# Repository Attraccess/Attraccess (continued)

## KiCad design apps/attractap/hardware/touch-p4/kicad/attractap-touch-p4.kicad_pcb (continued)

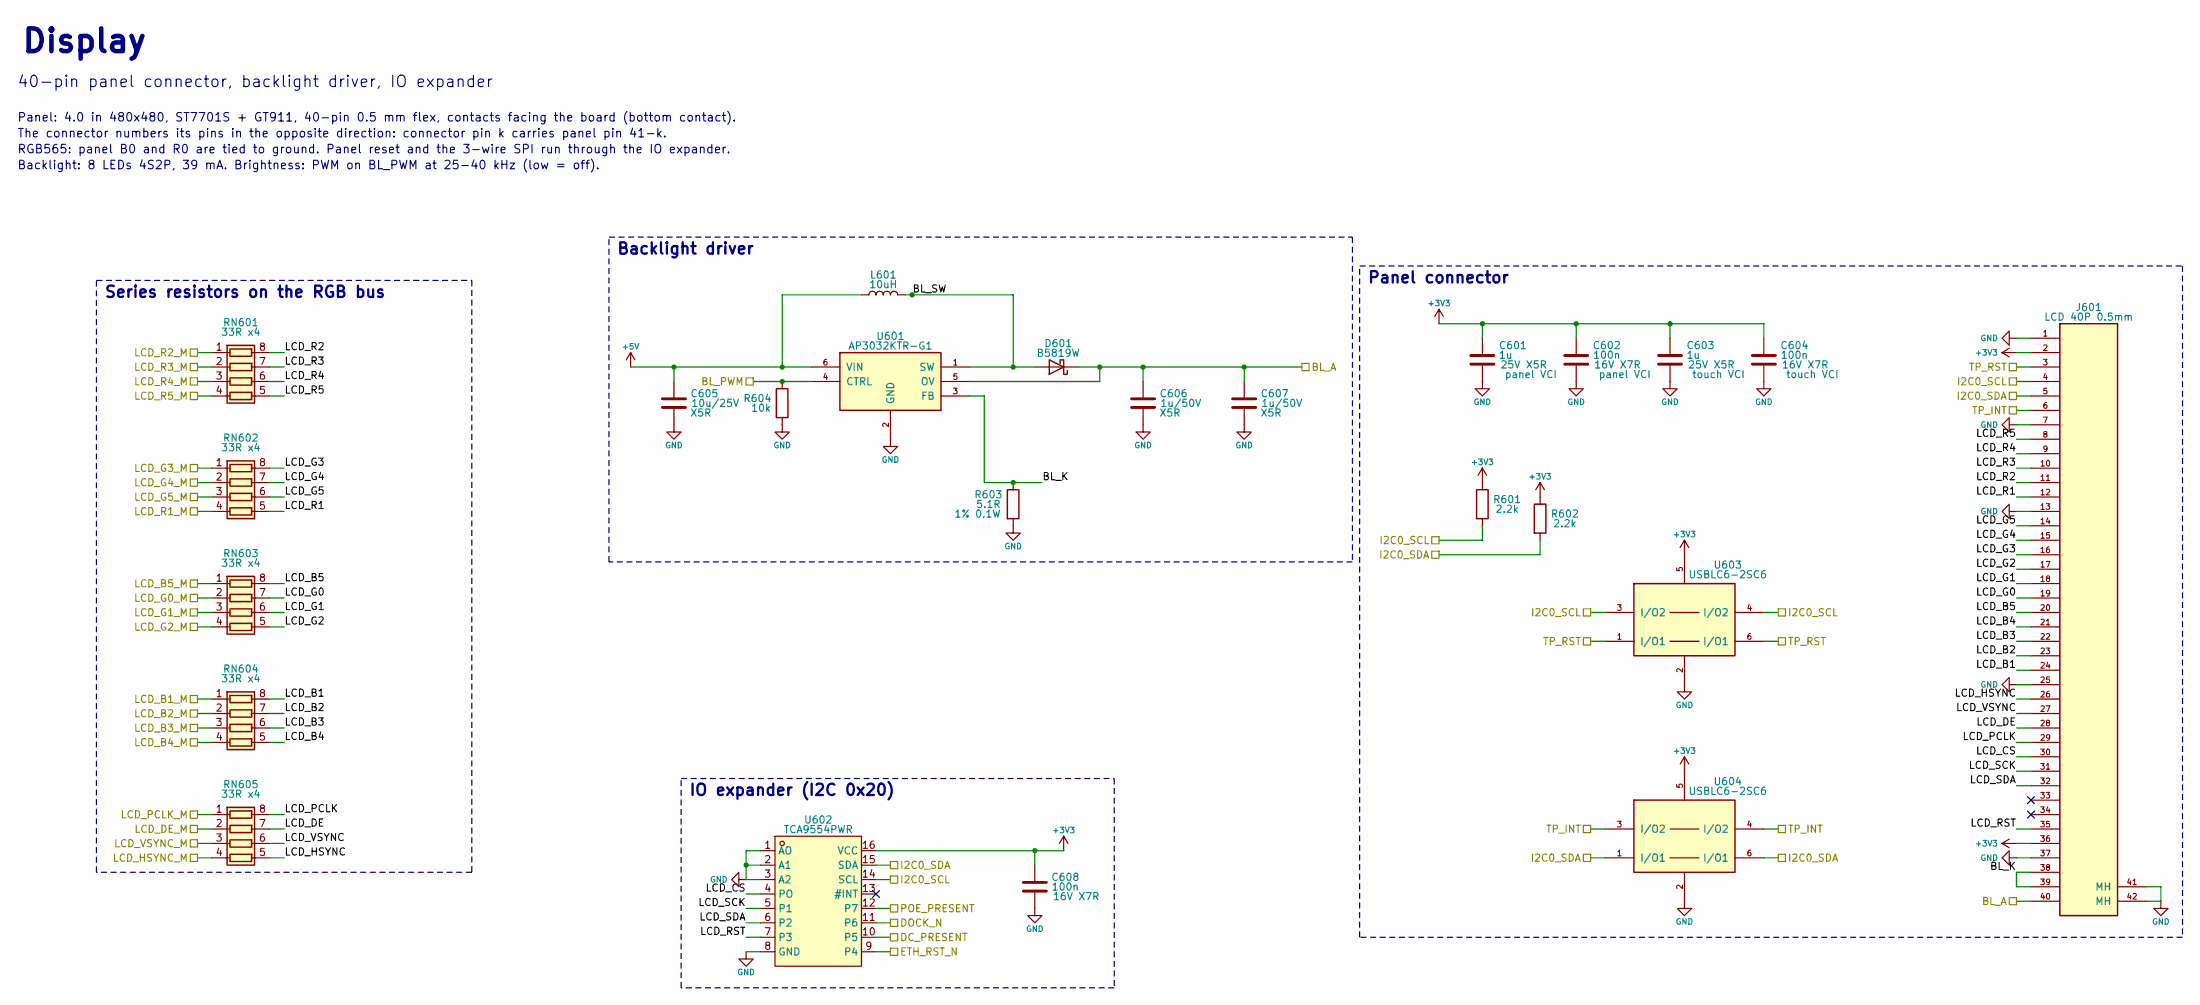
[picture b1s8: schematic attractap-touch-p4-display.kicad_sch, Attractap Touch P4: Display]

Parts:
C601, C603: 1u; C_0402_1005Metric; Rating 25V X5R; MPN CL05A105KA5NQNC; LCSC C52923
C602, C604, C608: 100n; C_0402_1005Metric; Rating 16V X7R; MPN CL05B104KO5NNNC; LCSC C1525
C605: 10u/25V; C_0805_2012Metric; Rating X5R; MPN CL21A106KAYNNNE; LCSC C15850
C606, C607: 1u/50V; C_0603_1608Metric; Rating X5R; MPN CL10A105KB8NNNC; LCSC C15849
D601: B5819W; SOD-123_L2.7-W1.6-LS3.7-RD-1; MPN B5819W; LCSC C8598
J601: LCD 40P 0.5mm; FPC-SMD_FH12-40S-0.5SH-55; MPN FH12-40S-0.5SH(55); LCSC C202114
L601: 10uH; IND-SMD_L3.0-W3.0_SWPA3010S; MPN SWPA3015S100MT; LCSC C45403
R601, R602: 2.2k; R_0402_1005Metric; Rating 1% 62.5mW; MPN 0402WGF2201TCE; LCSC C25879
R603: 5.1R; R_0603_1608Metric; Rating 1% 0.1W; MPN 0603WAF510KT5E; LCSC C25197
R604: 10k; R_0402_1005Metric; Rating 1% 62.5mW; MPN 0402WGF1002TCE; LCSC C25744
RN601, RN602, RN603, RN604, RN605: 33R x4; R_Array_Convex_4x0402; MPN 4D02WGJ0330TCE; LCSC C25501
U601: AP3032KTR-G1; SOT-23-6_L2.9-W1.6-P0.95-LS2.8-BR; MPN AP3032KTR-G1; LCSC C264086
U602: TCA9554PWR; TSSOP-16_L5.0-W4.4-P0.65-LS6.4-TL; MPN TCA9554PWR; LCSC C477924
U603, U604: USBLC6-2SC6; SOT-23-6_L2.9-W1.6-P0.95-LS2.8-BL; MPN USBLC6-2SC6; LCSC C7519

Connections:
+3V3: C601.1, C602.1, C603.1, C604.1, C608.1, J601.2, J601.36, R601.1, R602.1, U602.16 (VCC), U603.5, U604.5; also elsewhere on the board
+5V: C605.1, L601.1, U601.6 (VIN); also elsewhere on the board
/BL_A: C606.1, C607.1, D601.1 (K), J601.40, U601.5 (OV); also elsewhere on the board
/BL_PWM: R604.1, U601.4 (CTRL); also elsewhere on the board
/DC_PRESENT: U602.10 (P5); also elsewhere on the board
/DOCK_N: U602.11 (P6); also elsewhere on the board
/Display/BL_K: J601.38, J601.39, R603.1, U601.3 (FB)
/Display/BL_SW: D601.2 (A), L601.2, U601.1 (SW)
/Display/LCD_B1: J601.24, RN604.8 (R1.2)
/Display/LCD_B2: J601.23, RN604.7 (R2.2)
/Display/LCD_B3: J601.22, RN604.6 (R3.2)
/Display/LCD_B4: J601.21, RN604.5 (R4.2)
/Display/LCD_B5: J601.20, RN603.8 (R1.2)
/Display/LCD_CS: J601.30, U602.4 (PO)
/Display/LCD_DE: J601.28, RN605.7 (R2.2)
/Display/LCD_G0: J601.19, RN603.7 (R2.2)
/Display/LCD_G1: J601.18, RN603.6 (R3.2)
/Display/LCD_G2: J601.17, RN603.5 (R4.2)
/Display/LCD_G3: J601.16, RN602.8 (R1.2)
/Display/LCD_G4: J601.15, RN602.7 (R2.2)
/Display/LCD_G5: J601.14, RN602.6 (R3.2)
/Display/LCD_HSYNC: J601.26, RN605.5 (R4.2)
/Display/LCD_PCLK: J601.29, RN605.8 (R1.2)
/Display/LCD_R1: J601.12, RN602.5 (R4.2)
/Display/LCD_R2: J601.11, RN601.8 (R1.2)
/Display/LCD_R3: J601.10, RN601.7 (R2.2)
/Display/LCD_R4: J601.9, RN601.6 (R3.2)
/Display/LCD_R5: J601.8, RN601.5 (R4.2)
/Display/LCD_RST: J601.35, U602.7 (P3)
/Display/LCD_SCK: J601.31, U602.5 (P1)
/Display/LCD_SDA: J601.32, U602.6 (P2)
/Display/LCD_VSYNC: J601.27, RN605.6 (R3.2)
/ETH_RST_N: U602.9 (P4); also elsewhere on the board
/I2C0_SCL: J601.4, R601.2, U602.14 (SCL), U603.3 (I/O2), U603.4 (I/O2); also elsewhere on the board
/I2C0_SDA: J601.5, R602.2, U602.15 (SDA), U604.1 (I/O1), U604.6 (I/O1); also elsewhere on the board
/LCD_B1_M: RN604.1 (R1.1); also elsewhere on the board
/LCD_B2_M: RN604.2 (R2.1); also elsewhere on the board
/LCD_B3_M: RN604.3 (R3.1); also elsewhere on the board
/LCD_B4_M: RN604.4 (R4.1); also elsewhere on the board
/LCD_B5_M: RN603.1 (R1.1); also elsewhere on the board
/LCD_DE_M: RN605.2 (R2.1); also elsewhere on the board
/LCD_G0_M: RN603.2 (R2.1); also elsewhere on the board
/LCD_G1_M: RN603.3 (R3.1); also elsewhere on the board
/LCD_G2_M: RN603.4 (R4.1); also elsewhere on the board
/LCD_G3_M: RN602.1 (R1.1); also elsewhere on the board
/LCD_G4_M: RN602.2 (R2.1); also elsewhere on the board
/LCD_G5_M: RN602.3 (R3.1); also elsewhere on the board
/LCD_HSYNC_M: RN605.4 (R4.1); also elsewhere on the board
/LCD_PCLK_M: RN605.1 (R1.1); also elsewhere on the board
/LCD_R1_M: RN602.4 (R4.1); also elsewhere on the board
/LCD_R2_M: RN601.1 (R1.1); also elsewhere on the board
/LCD_R3_M: RN601.2 (R2.1); also elsewhere on the board
/LCD_R4_M: RN601.3 (R3.1); also elsewhere on the board
/LCD_R5_M: RN601.4 (R4.1); also elsewhere on the board
/LCD_VSYNC_M: RN605.3 (R3.1); also elsewhere on the board
/POE_PRESENT: U602.12 (P7); also elsewhere on the board
/TP_INT: J601.6, U604.3 (I/O2), U604.4 (I/O2); also elsewhere on the board
/TP_RST: J601.3, U603.1 (I/O1), U603.6 (I/O1); also elsewhere on the board
GND: C601.2, C602.2, C603.2, C604.2, C605.2, C606.2, C607.2, C608.2, J601.1, J601.7, J601.13, J601.25, J601.37, J601.41 (MH), J601.42 (MH), R603.2, R604.2, U601.2 (GND), U602.1 (AO), U602.2 (A1), U602.3 (A2), U602.8 (GND), U603.2, U604.2; also elsewhere on the board

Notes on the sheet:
Display
40-pin panel connector, backlight driver, IO expander
Panel: 4.0 in 480x480, ST7701S + GT911, 40-pin 0.5 mm flex, contacts facing the board (bottom contact).
The connector numbers its pins in the opposite direction: connector pin k carries panel pin 41-k.
RGB565: panel B0 and R0 are tied to ground. Panel reset and the 3-wire SPI run through the IO expander.
Backlight: 8 LEDs 4S2P, 39 mA. Brightness: PWM on BL_PWM at 25-40 kHz (low = off).
Panel connector
Series resistors on the RGB bus
Backlight driver
IO expander (I2C 0x20)

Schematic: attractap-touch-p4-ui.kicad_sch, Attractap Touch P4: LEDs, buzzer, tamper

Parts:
BZ701: MLT-8530; BUZ-SMD_4P-L8.5-W8.5-P8.50-BR; MPN MLT-8530; LCSC C94599
C701, C703, C704, C705, C706, C707, C708, C709, C710, C711, C713, C714, C716, C717, C718, C719, C720, C721, C722, C723, C724: 100n; C_0402_1005Metric; Rating 16V X7R; MPN CL05B104KO5NNNC; LCSC C1525
C702: 22u; C_0805_2012Metric; Rating 25V X5R; MPN CL21A226MAQNNNE; LCSC C45783
C712: 10u; C_0603_1608Metric; Rating 10V X5R; MPN CL10A106KP8NNNC; LCSC C19702
C715: 4.7u; C_0603_1608Metric; Rating 16V X5R; MPN CL10A475KO8NNNC; LCSC C19666
C725, C726: 100u/16V; CP_Elec_6.3x5.4; MPN FVH016ADA101M0654; LCSC C7469977
C727: 39p; C_0402_1005Metric; Rating 50V C0G; MPN CC0402JRNPO9BN390; LCSC C106223
D701, D702, D703, D704, D705, D706, D707, D708, D710, D711, D712, D713, D714, D715, D716, D717: SK6812MINI-E; LED_SK6812MINI-E_ReverseMount_Clear; MPN SK6812MINI-E; LCSC C5149201
D709: 1N4148W; SOD-123F_L2.7-W1.6-LS3.8-RD; MPN 1N4148W; LCSC C81598
Q701: AO3400A; SOT-23; MPN AO3400A; LCSC C20917
R701, R703: 100R; R_0402_1005Metric; Rating 1% 62.5mW; MPN 0402WGF1000TCE; LCSC C25076
R702: 10R; R_0603_1608Metric; Rating 5% 0.25W; MPN ESR03EZPJ100; LCSC C253327
R704, R705: 100k; R_0402_1005Metric; Rating 1% 62.5mW; MPN 0402WGF1003TCE; LCSC C25741
R706, R707: 10k; R_0402_1005Metric; Rating 1% 62.5mW; MPN 0402WGF1002TCE; LCSC C25744
R708: 91k; R_0402_1005Metric; Rating 1% 62.5mW; MPN 0402WGF9102TCE; LCSC C4147
R709: 2.2k; R_0402_1005Metric; Rating 1% 62.5mW; MPN 0402WGF2201TCE; LCSC C25879
TP814: ACC_INT; TestPoint_Pad_D1.5mm
TP815: PROX_INT; TestPoint_Pad_D1.5mm
U701: 74LV1T125; SOT-23-5_L3.0-W1.7-P0.95-LS2.8-BR; MPN SN74LV1T125DBVR; LCSC C473338
U702: LIS2DH12TR; LGA-12_2x2mm_P0.5mm; MPN LIS2DH12TR; LCSC C110926
U703: DRV5032FA; SOT-23; MPN DRV5032FADBZR; LCSC C140921
U704: VCNL4040M3OE; SENSORS-SMD_VCNL4040M3OE; MPN VCNL4040M3OE; LCSC C142526
U705: TPS2553DBVR; SOT-23-6_L2.9-W1.6-P0.95-LS2.8-BL; MPN TPS2553DBVR; LCSC C55266

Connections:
+3V3: C711.1, C712.1, C713.1, C714.1, C715.1, R706.1, R707.1, U702.2 (~CS), U702.9 (Vdd), U702.10 (Vdd_IO), U703.1 (VDD), U704.3 (VDD), U704.4 (ANODE); also elsewhere on the board
+5V: C702.1, C724.1, R702.1, U705.1 (IN), U705.3 (EN); also elsewhere on the board
/BUZZER: R703.1; also elsewhere on the board
/DOCK_N: U703.2 (OUT); also elsewhere on the board
/I2C0_SCL: U702.1 (SCL/SPC), U704.8 (SCLK); also elsewhere on the board
/I2C0_SDA: U702.4 (SDA/SDI), U704.7 (SDAT); also elsewhere on the board
/LED_DATA: R705.1, U701.2 (A); also elsewhere on the board
/UI/+5V_LED: C701.1, C703.1, C704.1, C705.1, C706.1, C707.1, C708.1, C709.1, C710.1, C716.1, C717.1, C718.1, C719.1, C720.1, C721.1, C722.1, C723.1, C725.1, C726.1, D701.3 (VDD), D702.3 (VDD), D703.3 (VDD), D704.3 (VDD), D705.3 (VDD), D706.3 (VDD), D707.3 (VDD), D708.3 (VDD), D710.3 (VDD), D711.3 (VDD), D712.3 (VDD), D713.3 (VDD), D714.3 (VDD), D715.3 (VDD), D716.3 (VDD), D717.3 (VDD), U701.5 (VCC), U705.6 (OUT)
/UI/ACC_INT: TP814.1, U702.12 (INT1)
/UI/ACC_SA0: R706.2, U702.3 (SA0/SDO)
/UI/BUZ_G: Q701.1 (G), R703.2, R704.1
/UI/BUZ_N: BZ701.2 (-), D709.2 (A), Q701.3 (D)
/UI/BUZ_P: BZ701.1 (+), D709.1 (K), R702.2
/UI/LED_D0: D701.2 (DIN), R701.2
/UI/LED_D1: D701.4 (DOUT), D702.2 (DIN)
/UI/LED_D2: D702.4 (DOUT), D703.2 (DIN)
/UI/LED_D3: D703.4 (DOUT), D704.2 (DIN)
/UI/LED_D4: D704.4 (DOUT), D705.2 (DIN)
/UI/LED_D5: D705.4 (DOUT), D706.2 (DIN)
/UI/LED_D6: D706.4 (DOUT), R709.1
/UI/LED_D6_F: C727.1, D707.2 (DIN), R709.2
/UI/LED_D7: D707.4 (DOUT), D708.2 (DIN)
/UI/LED_D8: D708.4 (DOUT), D710.2 (DIN)
/UI/LED_D9: D710.4 (DOUT), D711.2 (DIN)
/UI/LED_D10: D711.4 (DOUT), D712.2 (DIN)
/UI/LED_D11: D712.4 (DOUT), D713.2 (DIN)
/UI/LED_D12: D713.4 (DOUT), D714.2 (DIN)
/UI/LED_D13: D714.4 (DOUT), D715.2 (DIN)
/UI/LED_D14: D715.4 (DOUT), D716.2 (DIN)
/UI/LED_D15: D716.4 (DOUT), D717.2 (DIN)
/UI/LED_DATA_5V: R701.1, U701.4 (Y)
/UI/LED_ILIM: R708.1, U705.5 (ILIM)
/UI/PROX_INT: R707.2, TP815.1, U704.6 (INT)
/UI/PROX_K: U704.2 (CATHODE(SENSOR)), U704.5 (CATHODE(LED))
GND: C701.2, C702.2, C703.2, C704.2, C705.2, C706.2, C707.2, C708.2, C709.2, C710.2, C711.2, C712.2, C713.2, C714.2, C715.2, C716.2, C717.2, C718.2, C719.2, C720.2, C721.2, C722.2, C723.2, C724.2, C725.2, C726.2, C727.2, D701.1 (GND), D702.1 (GND), D703.1 (GND), D704.1 (GND), D705.1 (GND), D706.1 (GND), D707.1 (GND), D708.1 (GND), D710.1 (GND), D711.1 (GND), D712.1 (GND), D713.1 (GND), D714.1 (GND), D715.1 (GND), D716.1 (GND), D717.1 (GND), Q701.2 (S), R704.2, R705.2, R708.2, U701.1 (~OE), U701.3 (GND), U702.5 (RES), U702.6 (GND), U702.7 (GND), U702.8 (GND), U703.3 (GND), U704.1 (GND), U705.2 (GND); also elsewhere on the board

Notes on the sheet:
LEDs, buzzer, tamper
Addressable RGB LEDs, level shifter, buzzer driver, tamper sensors
16 reverse-mount LEDs in a ring, shining through the board. Data: D701 -> D708, D710 -> D717.
Buzzer: drive BUZZER with a 2.7 kHz square wave (LEDC). Its coil is between pads 1 and 2;
pads 3 and 4 only hold the part. R705 keeps the LED data line low while the MCU is in reset.
LED supply: U705 limits the ring to 255 to 334 mA (R ILIM 91 k); its enable is tied on.
R709 / C727 keep the NFC carrier off D707's data input, where the data line crosses the gap round the loop.
Tamper: U702 accelerometer on I2C0 at 0x19, events read over I2C (INT1 on TP814). U703 hall switch:
DOCK_N (IO expander P6) is low while the magnet in the dock is in front of it.
U704 proximity sensor on I2C0 at 0x60: infrared reflection from the dock plate 13.9 mm away, and ambient
light. Pins 2 and 5 are joined as the datasheet asks. INT is open drain, on TP815.
LED data level shifter and addressable LEDs
LED supply switch
Buzzer
Tamper detection

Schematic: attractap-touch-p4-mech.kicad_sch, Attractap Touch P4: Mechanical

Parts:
FID801, FID802, FID803, FID804, FID805: Fiducial; Fiducial_1mm_Mask2mm
H801, H802, H803, H804: M3; MountingHole_3.2mm_M3
TP816: VDC; TestPoint_Pad_D1.0mm
TP817: 5V_DC; TestPoint_Pad_D1.0mm
TP818: 5V_USB; TestPoint_Pad_D1.0mm
TP819: 5V_POE; TestPoint_Pad_D1.0mm
TP820: VDD_FLASH; TestPoint_Pad_D1.0mm
TP821: TVDD; TestPoint_Pad_D1.0mm
TP822: AVDD; TestPoint_Pad_D1.0mm
TP823: DVDD; TestPoint_Pad_D1.0mm
TP824: BL_A; TestPoint_Pad_D1.0mm
TP825: SDA; TestPoint_Pad_D1.0mm
TP826: SCL; TestPoint_Pad_D1.0mm
TP827: NFC_SDA; TestPoint_Pad_D1.0mm
TP828: NFC_SCL; TestPoint_Pad_D1.0mm
TP829: REF_CLK; TestPoint_Pad_D1.0mm
TP830: PHY_3V3; TestPoint_Pad_D1.0mm
TP831: 3V3_WIFI; TestPoint_Pad_D1.0mm

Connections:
/+3V3_WIFI: TP831.1; also elsewhere on the board
/+5V_DC: TP817.1; also elsewhere on the board
/+5V_POE: TP819.1; also elsewhere on the board
/+5V_USB: TP818.1; also elsewhere on the board
/BL_A: TP824.1; also elsewhere on the board
/I2C0_SCL: TP826.1; also elsewhere on the board
/I2C0_SDA: TP825.1; also elsewhere on the board
/NFC_AVDD: TP822.1; also elsewhere on the board
/NFC_DVDD: TP823.1; also elsewhere on the board
/NFC_SCL: TP828.1; also elsewhere on the board
/NFC_SDA: TP827.1; also elsewhere on the board
/NFC_TVDD: TP821.1; also elsewhere on the board
/PHY_3V3: TP830.1; also elsewhere on the board
/RMII_REF_CLK: TP829.1; also elsewhere on the board
/VDC: TP816.1; also elsewhere on the board
/VDD_FLASH: TP820.1; also elsewhere on the board

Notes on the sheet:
Mechanical
Mounting holes, fiducials and test points
Mounting holes (M3)
Fiducials
Test points: supply rails, I2C buses, RMII clock

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
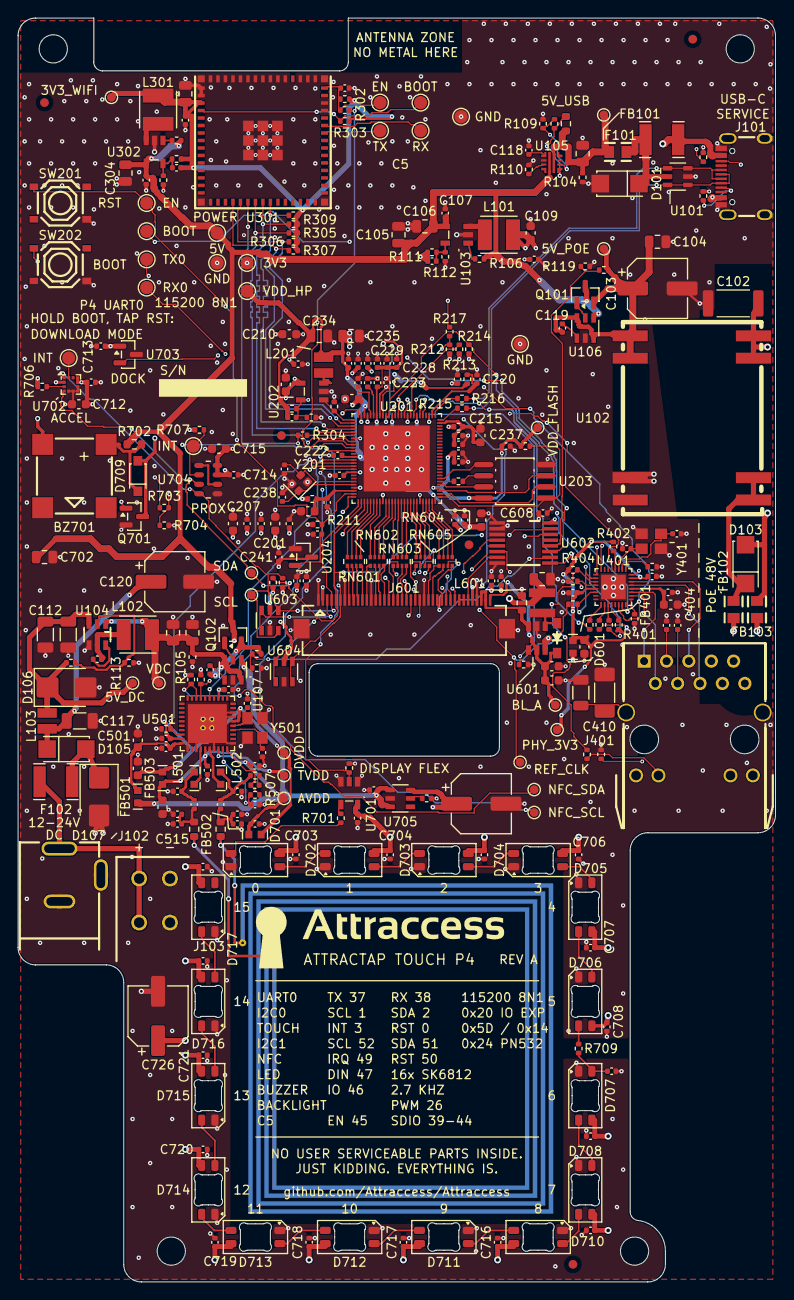
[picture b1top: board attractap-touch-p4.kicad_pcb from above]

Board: 6 copper layers, 86.0 x 143.5 mm, 335 parts (0 on the bottom side), 214 nets.

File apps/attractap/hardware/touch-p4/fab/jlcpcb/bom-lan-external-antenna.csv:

Comment,Designator,Footprint,LCSC Part #,Manufacturer Part
MLT-8530,BZ701,BUZ-SMD_4P-L8.5-W8.5-P8.50-BR,C94599,MLT-8530
10u/25V,"C101,C104,C106,C605",C_0805_2012Metric,C15850,
1n/2kV,"C102,C410",C_1206_3216Metric,C9196,
100u/16V,C103,CP_Elec_6.3x5.4,C7469977,FVH016ADA101M0654
22u,"C105,C109,C110,C115,C116,C234,C235,C301,C702",C_0805_2012Metric,C45783,
100n,"C107,C108,C111,C114,C202,C203,C204,C205,C206,C209,C211,C212,C214,C216,C219,C220,C221,C222,C225,C228,C229,C233,C237,C302,C402,C403,C405,C408,C409,C502,C504,C506,C508,C509,C521,C602,C604,C608,C701,C703,C704,C705,C706,C707,C708,C709,C710,C711,C713,C714",C_0402_1005Metric,C1525,
2.2u/100V,"C112,C113,C117",C_1206_3216Metric,C170101,CL31B225KCHSNNE
10u,"C201,C207,C208,C210,C213,C218,C232,C401,C404,C501,C503,C712,C715",C_0603_1608Metric,C19702,
4.7u,"C215,C507",C_0603_1608Metric,C19666,
10n,C217,C_0402_1005Metric,C15195,
1u,"C223,C224,C226,C227,C230,C231,C240,C303,C505,C601,C603",C_0402_1005Metric,C52923,
22p,C236,C_0402_1005Metric,C1555,
12p,"C238,C239",C_0402_1005Metric,C1547,
18p,"C406,C407,C510,C511",C_0402_1005Metric,C1549,
220p,"C512,C516",C_0402_1005Metric,C71693,
39p,"C513,C517",C_0402_1005Metric,C106223,
180p,"C514,C518",C_0402_1005Metric,C106999,
10p,"C515,C519",C_0402_1005Metric,C32949,
1n,C520,C_0402_1005Metric,C1523,
1u/50V,"C606,C607",C_0603_1608Metric,C15849,
SMAJ5.0A,D101,SMA_L4.3-W2.6-LS5.2-RD,C19077523,SMAJ5.0A
SS34,"D102,D104,D105,D107",SMA_L4.3-W2.6-LS5.2-RD,C8678,SS34
SMAJ58A,D103,SMA_L4.3-W2.6-LS5.2-RD,C19077554,SMAJ58A
SMBJ26A,D106,D_SMB,C315992,SMBJ26A
B5819W,D601,SOD-123_L2.7-W1.6-LS3.7-RD-1,C8598,B5819W
SK6812MINI-E,"D701,D702,D703,D704,D705,D706,D707,D708",LED_SK6812MINI-E_ReverseMount_Clear,C5149201,SK6812MINI-E
1N4148W,D709,SOD-123F_L2.7-W1.6-LS3.8-RD,C81598,1N4148W
2A PTC,F101,F1812,C89650,MF-MSMF200L-2
1.1A PTC 33V,F102,F1812,C21000,SMD1812P110TF/33
600R@100MHz 2A,"FB101,FB102,FB103",L0805,C21519,MPZ2012S601AT000
600R@100MHz,"FB401,FB501,FB502,FB503",L0603,C85833,BLM18KG601SN1D
USB-C,J101,USB-C_SMD-TYPE-C-31-M-12_1,C165948,TYPE-C-31-M-12
DC jack 5.5/2.1,J102,DC-IN-TH_PJ-002A,C3096082,PJ-002A
DC terminal,J103,CONN-TH_4P-P3.5-2601-3102,C2765061,250-202
HY931147C,J401,RJ45-TH_HY931147C,C91754,HY931147C
LCD 40P 0.5mm,J601,FPC-SMD_FH12-40S-0.5SH-55,C202114,FH12-40S-0.5SH(55)
4.7uH 4A,L101,IND-SMD_L4.0-W4.0,C354583,CKCSA4020-4.7uH/M
6.8uH 2.4A,L102,IND-SMD_L4.0-W4.0,C5291940,CKCSA4020-6.8uH/M
2.2uH 2.3A,"L103,L201",IND-SMD_L2.5-W2.0_CKCSA252012,C354540,CKCSA252012-2.2uH/M
560nH,"L501,L502",IND-SMD_L1.6-W0.8-1,C91630,LQW18CNR56J00D
10uH,L601,IND-SMD_L3.0-W3.0_SWPA3010S,C45403,SWPA3015S100MT
AO3400A,Q701,SOT-23,C20917,AO3400A
5.1k,"R101,R102,R402,R403,R404,R405,R406",R_0402_1005Metric,C25905,
100k,"R103,R106,R206,R704,R705",R_0402_1005Metric,C25741,
4.7k,"R104,R105",R_0402_1005Metric,C25900,
0R,"R201,R202,R203,R208,R209,R210",R_0402_1005Metric,C17168,
510k,"R204,R205",R_0402_1005Metric,C11616,
10k,"R207,R211,R212,R213,R301,R303,R503,R604,R706,R707",R_0402_1005Metric,C25744,
1.5k,R214,R_0402_1005Metric,C25867,
22R,"R215,R216,R304",R_0402_1005Metric,C25092,
1k,"R217,R302,R411,R412,R507",R_0402_1005Metric,C11702,
51k,"R305,R306,R307,R308,R309",R_0402_1005Metric,C25794,
6.19k,R401,R_0402_1005Metric,C25914,
33R,"R407,R408,R409,R410",R_0402_1005Metric,C25105,
1M,R413,R_1206_3216Metric,C17927,
2.2k,"R501,R502,R601,R602",R_0402_1005Metric,C25879,
1.5R,"R504,R505",R_0603_1608Metric,C22769,
3.9k,R506,R_0402_1005Metric,C51721,
5.1R,R603,R_0603_1608Metric,C25197,
100R,"R701,R703",R_0402_1005Metric,C25076,
10R,R702,R_0603_1608Metric,C253327,ESR03EZPJ100
33R x4,"RN601,RN602,RN603,RN604,RN605",R_Array_Convex_4x0402,C25501,4D02WGJ0330TCE
RESET / BOOT,"SW201,SW202",SW-SMD_4P-L5.1-W5.1-P3.70-LS6.5-TL_H1.5,C318884,TS-1187A-B-A-B
USBLC6-2SC6,U101,SOT-23-6_L2.9-W1.6-P0.95-LS2.8-BL,C7519,USBLC6-2SC6
DP9900M-5V,U102,PWRM-SMD_DP9900M-5V,C5380106,DP9900M-5V
AP63203WU-7,U103,TSOT-26_L2.9-W1.6-P0.95-LS2.8-BL,C780769,AP63203WU-7
AP63205WU-7,U104,TSOT-26_L2.9-W1.6-P0.95-LS2.8-BL,C2071056,AP63205WU-7
ESP32-P4NRW32X,U201,QFN-104_L10.0-W10.0-P0.35-TL-EP7.5,C54540373,ESP32-P4NRW32X
TLV62569DBVR,U202,SOT-23-5_L3.0-W1.7-P0.95-LS2.8-BR,C141836,TLV62569DBVR
W25Q128JVSIQ,U203,SOIC-8_L5.3-W5.3-P1.27-LS8.0-BL,C97521,W25Q128JVSIQ
ESP32-C6-MINI-1U-H4,U301,WIFIM-SMD_61P-L16.6-W13.2-P0.80-ESP32-C6-MINI-1-N4,C20627095,ESP32-C6-MINI-1U-H4
IP101GRI,U401,QFN-32_L4.0-W4.0-P0.40-BL-EP2.7,C703537,IP101GRI
PN5321A3HN/C106,U501,QFN-40_L6.0-W6.0-P0.50-BL-EP,C53457895,PN5321A3HN (Tokmas)
AP3032KTR-G1,U601,SOT-23-6_L2.9-W1.6-P0.95-LS2.8-BR,C264086,AP3032KTR-G1
TCA9554PWR,U602,TSSOP-16_L5.0-W4.4-P0.65-LS6.4-TL,C477924,TCA9554PWR
74LV1T125,U701,SOT-23-5_L3.0-W1.7-P0.95-LS2.8-BR,C473338,SN74LV1T125DBVR
LIS2DH12TR,U702,LGA-12_2x2mm_P0.5mm,C110926,LIS2DH12TR
DRV5032FA,U703,SOT-23,C140921,DRV5032FADBZR
VCNL4040M3OE,U704,SENSORS-SMD_VCNL4040M3OE,C142526,VCNL4040M3OE
40MHz 9pF 10ppm,Y201,CRYSTAL-SMD_4P-L3.2-W2.5-BL-2,C255943,X1E000021017700
25MHz 12pF,Y401,CRYSTAL-SMD_4P-L3.2-W2.5-BL,C9006,X322525MOB4SI
27.12MHz 12pF,Y501,CRYSTAL-SMD_4P-L3.2-W2.5-BL,C113669,X32252712MOB4SI

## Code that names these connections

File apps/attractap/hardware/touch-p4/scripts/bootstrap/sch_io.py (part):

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    cv.hang(P_['C502'], x + 43.18, y)
    cv.wire((x, y), 'FB501.1')
    cv.wire('FB501.2', (x + 55.88, y))
    cv.label('NFC_VBAT', x + 55.88, y, 'R')
    for k, (fb, caps, net) in enumerate((('FB502', ['C505', 'C506'], 'NFC_AVDD'),
                                         ('FB503', ['C507', 'C508'], 'NFC_TVDD'))):
        yy = y + 22.86 + 22.86 * k
        cv.label('NFC_DVDD', x, yy, 'L')
        cx = x + 7.62
        if k == 0:
            for c in ('C503', 'C504'):
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    yp, yn = y, y + 12.7
    xc = x + 12.7
    cv.put(P_['Y501'], xc, (yp + yn) / 2, 270, fields='r')
    cv.label('NFC_X1', x, yp, 'L')
    cv.label('NFC_X2', x, yn, 'L')
    cv.wire((x, yp), (xc, yp), 'Y501.1')
    cv.wire((x, yn), (xc, yn), 'Y501.3')
    cv.wire((xc, yp), (xc + 27.94, yp))
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        cv.wire((x, yy), (xr, yy))
        cv.stand(P_[r], xr, yy, fields='r')
    yr = y + 15.24
    cv.label('NFC_RST', x, yr, 'L')
    cv.wire((x, yr), (x + 7.62, yr))
    cv.hang(P_['R503'], x + 7.62, yr, gap=0)

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        cv.wire(l0 + '.2', c1 + '.1')
        cv.wire(c1 + '.2', rq + '.1')
    ant = cv.put(P_['ANT501'], xant, yant, 270, fields='r')
    p1, p2 = ant.pin('1'), ant.pin('2')             # p1 (NFC_ANT2) above p2 (NFC_ANT1)
    cv.wire('R505.2', (xant - 22.86, ya), (xant - 22.86, p1[1]), p1)
    cv.wire('R504.2', (xant - 15.24, yb), (xant - 15.24, p2[1]), p2)
    # receiver: divider from the TX2 filter node, coupling capacitor, bias from VMID
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    cv.inline(P_['R507'], x + 73.66, yr, fields='a')
    cv.wire('C520.2', 'R507.1')
    cv.wire((x + 60.96, yr), (x + 60.96, yr - 7.62))
    cv.label('NFC_RX', x + 60.96, yr - 7.62, 'U')
    cv.hang(P_['C521'], x + 83.82, yr, gap=0)
    cv.wire('R507.2', (x + 96.52, yr))
    cv.label('NFC_VMID', x + 96.52, yr, 'R')


# ---- Display -----------------------------------------------------------------------------------------
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    cv.hang(P_['C606'], xo + 7.62, sw[1])
    cv.hang(P_['C607'], xo + 25.4, sw[1])
    cv.wire('D601.1', (xo + 35.56, sw[1]))
    cv.label('BL_A', xo + 35.56, sw[1], 'R')
    yk = fb[1] + 15.24
    cv.wire(fb, (fb[0] + P, fb[1]), (fb[0] + P, yk), (fb[0] + 12.7, yk))
    cv.hang(P_['R603'], fb[0] + 7.62, yk, gap=0, fields='l')
    cv.label('BL_K', fb[0] + 12.7, yk, 'R')
    cv.wire(ctrl, (ctrl[0] - 5.08, ctrl[1]))
    cv.hang(P_['R604'], ctrl[0] - 5.08, ctrl[1], gap=0, fields='l')
    cv.wire((ctrl[0] - 5.08, ctrl[1]), (ctrl[0] - 10.16, ctrl[1]))
    cv.label('BL_PWM', ctrl[0] - 10.16, ctrl[1], 'L')


def expander(cv, P_, x, y):
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    cv.begin('LED data level shifter and addressable LEDs')
    u = cv.put(P_['U701'], x + 25.4, y - P)
    a, yo, vcc = u.pin('2'), u.pin('4'), u.pin('5')
    cv.label('LED_DATA', x, a[1], 'L')
    cv.wire((x, a[1]), a)
    cv.hang(P_['R705'], x + 5.08, a[1], gap=0, fields='l')
    yc = vcc[1] - 10.16
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
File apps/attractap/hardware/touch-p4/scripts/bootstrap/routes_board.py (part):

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    # The inner-layer track starts inside the pin's pad on the side away from the jack's shield pad GND2:
    # from the pin's centre its 0.6 mm would come 2.6 mm from that pad, from there 3.06 mm.
    g2 = p('J401', 'GND2')
    for name, pin, bead in (('POE_VP', j9, f2a), ('POE_VN', j10, f3a)):
        xv = bead[0]
        dx, dy = pin[0] - g2[0], pin[1] - g2[1]
        k = 0.5 / math.hypot(dx, dy)
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        B.track([vp, (xi, yp)], name + 'P', w, layer=B_)
        B.track([neg, (xi - d_neg, neg[1]), (xi, neg[1] + d_neg), (xi, yc)], name + 'N', w)
        B.via(xi, yc, name + 'N')
        # MDI_TN passes the jack's PoE pin 9: 0.1 mm further left keeps it 3 mm from it (3.06 mm)
        s = 0.1 if name == 'MDI_T' else 0.0
        B.track([(xi, yc), (xo - s, yc + (xo - s - xi)), (xo - s, yn - 1.0), (xo, yn)], name + 'N', w, layer=B_)
    # centre taps: from the capacitors straight down to jack pins 3 and 4
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    p = B.pad
    top, bot = sorted(B.pads_num('J103', '1'), key=lambda q: q[1])
    jack, f1 = p('J102', '1'), p('F102', '1')
    B.track([bot, top, (top[0], jack[1]), jack], 'VDC_IN', w)     # both pins of the + pole, then the jack
    B.track(dog(jack, f1), 'VDC_IN', w)
    B.track(dog(p('F102', '2'), p('D105', '2')), 'VDC_F', w)
    # input TVS: its VDC_F pad below and right of the diode's, its ground pad straight down into the plane
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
